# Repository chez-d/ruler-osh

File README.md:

# ruler-osh
OSH version of my personal PCB ruler

Use it for what you want, but it would be nice to credit me.
It's a 15cm ruler - but also a FPGA dev board, music player, game console, and component footprint reference...
Best on OSHPark After Dark.

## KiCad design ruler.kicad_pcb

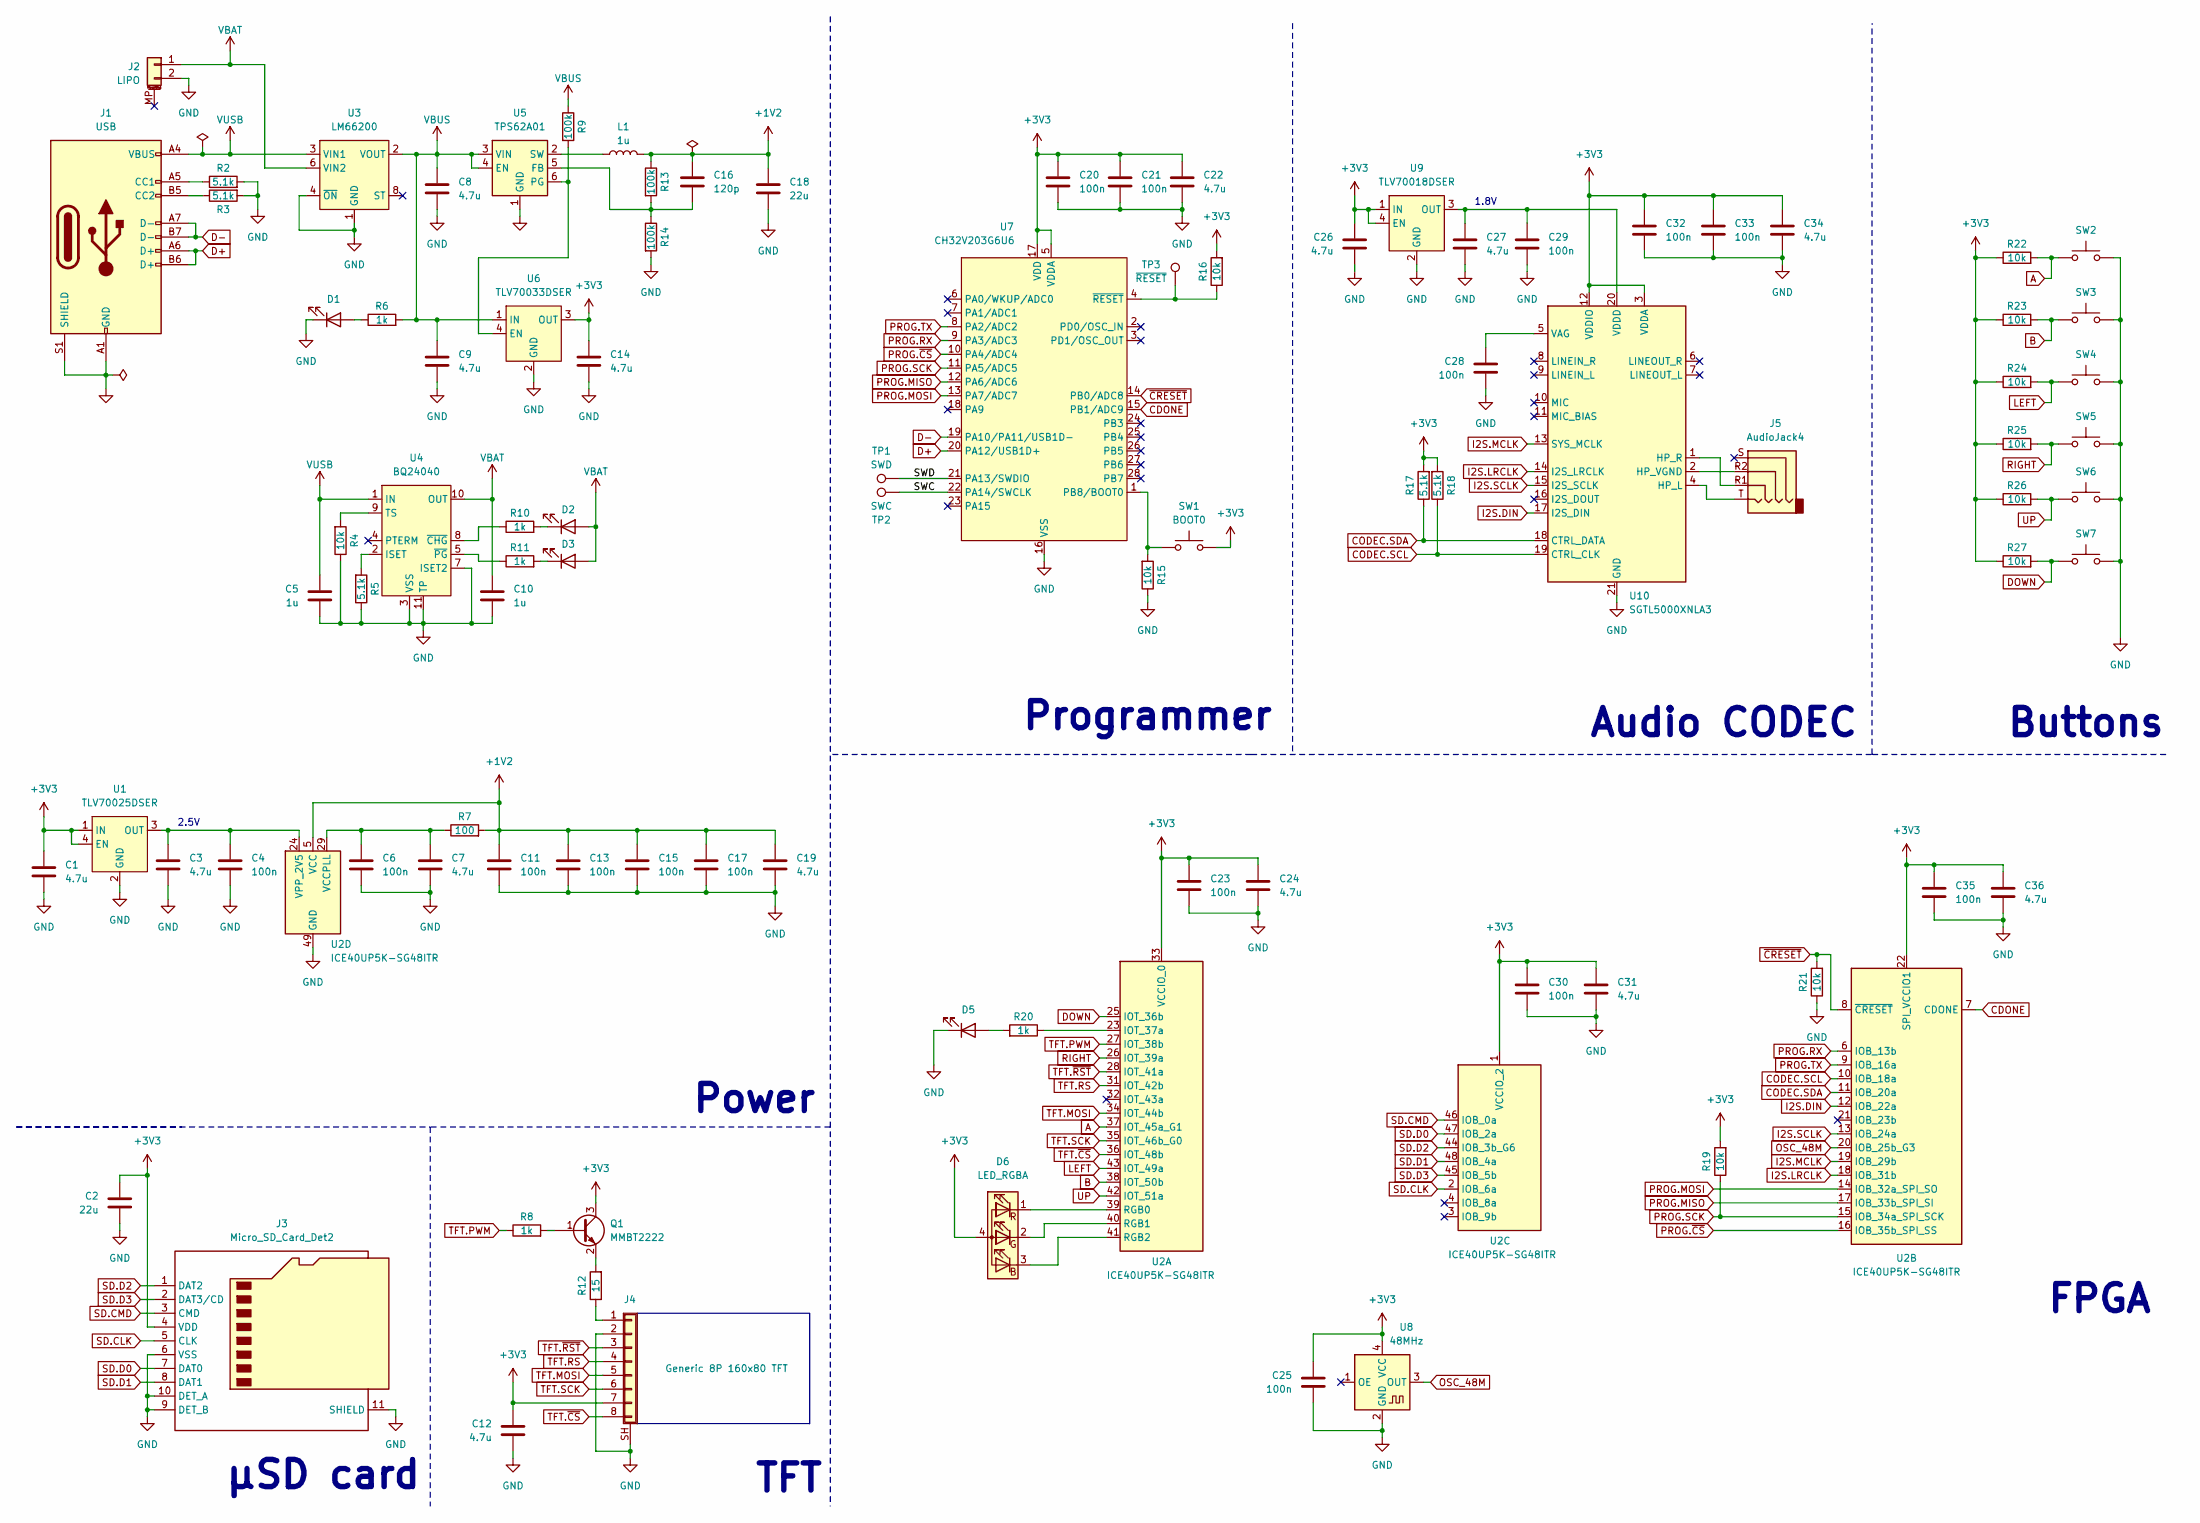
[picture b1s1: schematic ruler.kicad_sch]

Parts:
C1, C3, C7, C8, C9, C12, C14, C19, C22, C24, C26, C27, C31, C34, C36: 4.7u; C_0402_1005Metric
C2, C18: 22u; C_0805_2012Metric
C4, C6, C11, C13, C15, C17, C20, C21, C23, C25, C28, C29, C30, C32, C33, C35: 100n; C_0402_1005Metric
C5, C10: 1u; C_0402_1005Metric
C16: 120p; C_0402_1005Metric
D1, D5: LED; LED_0603_1608Metric
D2: ORANGE; LED_0603_1608Metric
D3: GREEN; LED_0603_1608Metric
D6: LED_RGBA; XL-B1515RGBA-HF
J1: USB; USB_C_Receptacle_HCTL_HC-TYPE-C-16P-01A
J2: LIPO; JST_PH_S2B-PH-SM4-TB_1x02-1MP_P2.00mm_Horizontal
J3: Micro_SD_Card_Det2; microSD_HC_Molex_104031-0811
J4: Generic 8P 160x80 TFT; LCD_1x8_Newvision
J5: AudioJack4; Jack_3.5mm_PJ320D_Horizontal
L1: 1u; L_Murata_DFE201610P
Q1: MMBT2222; SOT-723
R2, R3, R5, R17, R18: 5.1k; R_0402_1005Metric
R4, R15, R16, R19, R21, R22, R23, R24, R25, R26, R27: 10k; R_0402_1005Metric
R6, R8, R10, R11, R20: 1k; R_0402_1005Metric
R7: 100; R_0402_1005Metric
R9, R13, R14: 100k; R_0402_1005Metric
R12: 15; R_0402_1005Metric
SW1: BOOT0; SW_SPST_PTS815
SW2, SW3, SW4, SW5, SW6, SW7: SW_Push; SW_SPST_PTS815
TP1: SWD; TestPoint
TP2: SWC; TestPoint
TP3: ~{RESET}; TestPoint
U1: TLV70025DSER; WSON-6_1.5x1.5mm_P0.5mm
U2: ICE40UP5K-SG48ITR; QFN-48-1EP_7x7mm_P0.5mm_EP5.6x5.6mm
U3: LM66200; SOT-583-8
U4: BQ24040; WSON-10_EP_2x2_Pitch0.4mm
U5: TPS62A01; SOT-563
U6: TLV70033DSER; WSON-6_1.5x1.5mm_P0.5mm
U7: CH32V203G6U6; QFN-28-1EP_4x4mm_P0.4mm_EP2.8x2.8mm
U8: 48MHz; Crystal_SMD_2016-4Pin_2.0x1.6mm
U9: TLV70018DSER; WSON-6_1.5x1.5mm_P0.5mm
U10: SGTL5000XNLA3; QFN-20-1EP_3x3mm_P0.4mm_EP1.65x1.65mm

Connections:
+1V2: C11.1, C13.1, C15.1, C16.1, C17.1, C18.1, C19.1, L1.2, R7.2, R13.1, U2.5 (VCC), U2.30 (VCC)
+3V3: C1.1, C2.1, C12.1, C14.1, C20.1, C21.1, C22.1, C23.1, C24.1, C25.1, C26.1, C30.1, C31.1, C32.1, C33.1, C34.1, C35.1, C36.1, D6.4 (A), J3.4 (VDD), J4.7, Q1.3 (C), R16.2, R17.2, R18.2, R19.2, R22.1, R23.1, R24.1, R25.1, R26.1, R27.1, SW1.2, U1.1 (IN), U1.4 (EN), U2.1 (VCCIO_2), U2.22 (SPI_VCCIO1), U2.33 (VCCIO_0), U6.3 (OUT), U7.5 (VDDA), U7.17 (VDD), U8.4 (VCC), U9.1 (IN), U9.4 (EN), U10.3 (VDDA), U10.12 (VDDIO)
/SWC: TP2.1, U7.22 (PA14/SWCLK)
/SWD: TP1.1, U7.21 (PA13/SWDIO)
A: R22.2, SW2.1, U2.37 (IOT_45a_G1)
B: R23.2, SW3.1, U2.38 (IOT_50b)
CDONE: U2.7 (CDONE), U7.15 (PB1/ADC9)
CODEC.SCL: R18.1, U2.10 (IOB_18a), U10.19 (CTRL_CLK)
CODEC.SDA: R17.1, U2.11 (IOB_20a), U10.18 (CTRL_DATA)
D+: J1.A6 (D+), J1.B6 (D+), U7.20 (PA12/USB1D+)
D-: J1.A7 (D-), J1.B7 (D-), U7.19 (PA10/PA11/USB1D-)
DOWN: R27.2, SW7.1, U2.25 (IOT_36b)
GND: C1.2, C2.2, C3.2, C4.2, C5.2, C6.2, C7.2, C8.2, C9.2, C10.2, C11.2, C12.2, C13.2, C14.2, C15.2, C17.2, C18.2, C19.2, C20.2, C21.2, C22.2, C23.2, C24.2, C25.2, C26.2, C27.2, C28.2, C29.2, C30.2, C31.2, C32.2, C33.2, C34.2, C35.2, C36.2, D1.1 (K), D5.1 (K), J1.A1 (GND), J1.A12 (GND), J1.B1 (GND), J1.B12 (GND), J1.S1 (SHIELD), J2.2, J3.6 (VSS), J3.9 (DET_B), J3.10 (DET_A), J3.11 (SHIELD), J4.2, J4.SH (Shield), R2.2, R3.2, R4.1, R5.1, R14.2, R15.1, R21.1, SW2.2, SW3.2, SW4.2, SW5.2, SW6.2, SW7.2, U1.2 (GND), U1.5 (NC), U1.6 (NC), U2.49 (GND), U3.1 (GND), U3.4 (~ON), U3.5 (GND), U4.3 (VSS), U4.7 (ISET2), U4.11 (TP), U5.1 (GND), U6.2 (GND), U6.5 (NC), U6.6 (NC), U7.16 (VSS), U7.29 (VSS), U8.2 (GND), U9.2 (GND), U9.5 (NC), U9.6 (NC), U10.21 (GND)
I2S.DIN: U2.12 (IOB_22a), U10.17 (I2S_DIN)
I2S.LRCLK: U2.18 (IOB_31b), U10.14 (I2S_LRCLK)
I2S.MCLK: U2.19 (IOB_29b), U10.13 (SYS_MCLK)
I2S.SCLK: U2.13 (IOB_24a), U10.15 (I2S_SCLK)
LEFT: R24.2, SW4.1, U2.43 (IOT_49a)
unnamed: D1.2 (A), R6.1
unnamed: D2.1 (K), R10.2
unnamed: D3.1 (K), R11.2
unnamed: D5.2 (A), R20.2
unnamed: D6.3 (BK), U2.41 (RGB2)
unnamed: D6.2 (GK), U2.40 (RGB1)
unnamed: D6.1 (RK), U2.39 (RGB0)
unnamed: J1.A5 (CC1), R2.1
unnamed: J1.B5 (CC2), R3.1
unnamed: J4.1, R12.1
unnamed: Q1.1 (B), R8.2
unnamed: Q1.2 (E), R12.2
unnamed: C3.1, C4.1, U1.3 (OUT), U2.24 (VPP_2V5)
unnamed: R20.1, U2.23 (IOT_37a)
unnamed: C6.1, C7.1, R7.1, U2.29 (VCCPLL)
unnamed: R5.2, U4.2 (ISET)
unnamed: R4.2, U4.9 (TS)
unnamed: R10.1, U4.8 (~CHG)
unnamed: R11.1, U4.5 (~PG)
unnamed: C16.2, R13.2, R14.1, U5.5 (FB)
unnamed: R9.2, U5.6 (PG), U6.4 (EN)
unnamed: L1.1, U5.2 (SW)
unnamed: R15.2, SW1.1, U7.1 (PB8/BOOT0)
unnamed: R16.1, TP3.1, U7.4 (~RESET)
unnamed: J5.T, U10.4 (HP_L)
unnamed: J5.R1, U10.1 (HP_R)
unnamed: J5.R2, U10.2 (HP_VGND)
unnamed: C28.1, U10.5 (VAG)
unnamed: C27.1, C29.1, U9.3 (OUT), U10.20 (VDDD)
OSC_48M: U2.20 (IOB_25b_G3), U8.3 (OUT)
PROG.MISO: U2.17 (IOB_33b_SPI_SI), U7.12 (PA6/ADC6)
PROG.MOSI: U2.14 (IOB_32a_SPI_SO), U7.13 (PA7/ADC7)
PROG.RX: U2.6 (IOB_13b), U7.9 (PA3/ADC3)
PROG.SCK: R19.1, U2.15 (IOB_34a_SPI_SCK), U7.11 (PA5/ADC5)
PROG.TX: U2.9 (IOB_16a), U7.8 (PA2/ADC2)
PROG.~CS: U2.16 (IOB_35b_SPI_SS), U7.10 (PA4/ADC4)
RIGHT: R25.2, SW5.1, U2.26 (IOT_39a)
SD.CLK: J3.5 (CLK), U2.2 (IOB_6a)
SD.CMD: J3.3 (CMD), U2.46 (IOB_0a)
SD.D0: J3.7 (DAT0), U2.47 (IOB_2a)
SD.D1: J3.8 (DAT1), U2.48 (IOB_4a)
SD.D2: J3.1 (DAT2), U2.44 (IOB_3b_G6)
SD.D3: J3.2 (DAT3/CD), U2.45 (IOB_5b)
TFT.MOSI: J4.5, U2.34 (IOT_44b)
TFT.PWM: R8.1, U2.27 (IOT_38b)
TFT.RS: J4.4, U2.31 (IOT_42b)
TFT.SCK: J4.6, U2.35 (IOT_46b_G0)
TFT.~CS: J4.8, U2.36 (IOT_48b)
TFT.~RST: J4.3, U2.28 (IOT_41a)
UP: R26.2, SW6.1, U2.42 (IOT_51a)
VBAT: C10.1, D2.2 (A), D3.2 (A), J2.1, U3.6 (VIN2), U4.10 (OUT)
VBUS: C8.1, C9.1, R6.2, R9.1, U3.2 (VOUT), U3.7 (VOUT), U5.3 (VIN), U5.4 (EN), U6.1 (IN)
VUSB: C5.1, J1.A4 (VBUS), J1.A9 (VBUS), J1.B4 (VBUS), J1.B9 (VBUS), U3.3 (VIN1), U4.1 (IN)
~CRESET: R21.2, U2.8 (~CRESET), U7.14 (PB0/ADC8)

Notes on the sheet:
Power
Buttons
1.8V
2.5V
Programmer
FPGA
TFT
µSD card
Audio CODEC

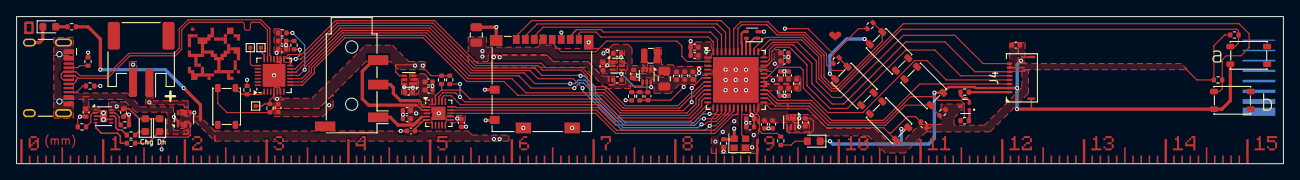
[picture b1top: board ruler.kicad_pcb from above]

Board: 2 copper layers, 155.0 x 18.0 mm, 95 parts (0 on the bottom side), 72 nets.

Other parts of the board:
PCB1: Ruler
